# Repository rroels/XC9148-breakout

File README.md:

# Torex XC9148 Breakout Board

> [!WARNING]
> The information and material (code, designs, files, ...) are provided "AS IS". We make no representation or warranty of any kind, express or implied, regarding the accuracy, adequacy, validity, reliability, availability, or completeness of any information or material. Use this at your own risk.

> [!WARNING]
> At the time of writing this PCB has not even been produced yet, and as such, it has not even been tested yet! Once it has been properly tested, I will confirm that everything works as expected.

> [!WARNING]
> This board was designed for the XC9148G50CER variant of the XC9148. This has some characteristics that are important for the design of this breakout board (e.g. its output voltage, oscillation frequency and lack of bypass mode). 

## Introduction

This is a breakout board for the Torex XC9148 voltage convertor.

[https://product.torexsemi.com/en/series/xc9148](https://product.torexsemi.com/en/series/xc9148)

## Change Log

* v1.1
  * Increased pad sizes of XC9148 for easier soldering by hand
* v1.0
  * Initial design 

## Design Considerations

* Designed specifically for the XC9148G50CER variant of the XC9148
  * 0.9 - 6V input  
  * fixed 5V output
  * 1.2MHz oscillation frequency
  * no bypass mode

> [!WARNING]
> The 3.0MHz variations of the XC9148 will not work on this board!  

## Schematics 

## How to Obtain the Physical PCB

The Gerber file is in this repository (`gerbers/XC9148-breakout.zip`). Simply upload this file a PCB manufacturer of your choice (JLPCB, PCBWay, ...), and you they will make it for you for as low as \$5 for 5 pieces (with the cheapest shipping option, which can take a few weeks).

For JLCPCB, select the order number option where they will replace "JLCJLCJLCJLC" on the board with the actual order number.

> [!WARNING]
> Note that will still have to solder the components onto the PCB yourself!

## How to Edit Design

Everything you need to edit this design in KiCad 8 is included in the repository.

However, this project uses symbols, footprints and 3D models from [Component Search Engine](https://componentsearchengine.com/). Their license allows us to do pretty much whatever we want with them, except redistributing them. For this reason I can't include them in this repository.

If you would like to edit the design yourself, you will need to download the following component libraries from [https://componentsearchengine.com/](https://componentsearchengine.com/) (it's free!):

* [https://componentsearchengine.com/part-view/XC9148G50CER-G/Torex](https://componentsearchengine.com/part-view/XC9148G50CER-G/Torex)

From the downloaded zip files, move the content of the `KiCad` and `3D` subfolders into the project structure, so that the end-result looks like this:

The KiCad project is configured to look for these files in these locations, using relative paths, so no changes to the project itself are required.	

## Sources

* [https://product.torexsemi.com/en/series/xc9148](https://product.torexsemi.com/en/series/xc9148)

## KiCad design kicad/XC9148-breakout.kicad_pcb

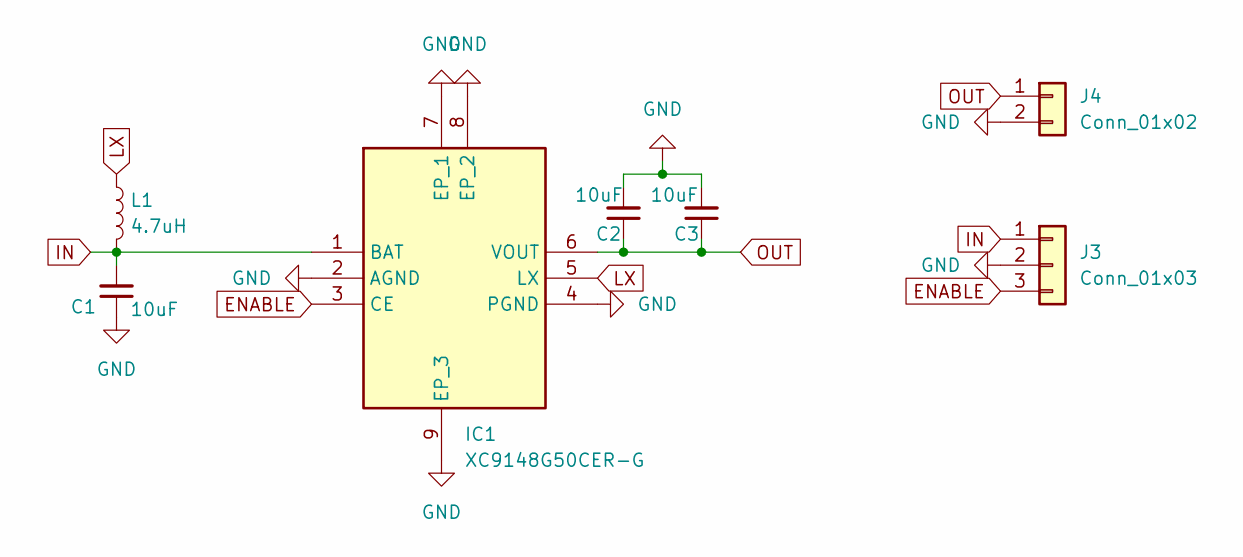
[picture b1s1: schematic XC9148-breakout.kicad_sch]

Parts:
C1, C2, C3: 10uF; C_0603_1608Metric_Pad1.08x0.95mm_HandSolder
IC1: XC9148G50CER-G; XC9147_8_USP-6C; Manufacturer_Part_Number XC9148G50CER-G; Mouser Part Number 865-XC9148G50CER-G
J3: Conn_01x03; PinHeader_1x03_P2.54mm_Vertical
J4: Conn_01x02; PinHeader_1x02_P2.54mm_Vertical
L1: 4.7uH; L_1008_2520Metric_Pad1.43x2.20mm_HandSolder

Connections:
ENABLE: IC1.3 (CE), J3.3
GND: C1.1, C2.2, C3.2, IC1.2 (AGND), IC1.4 (PGND), IC1.7 (EP_1), IC1.8 (EP_2), IC1.9 (EP_3), J3.2, J4.2
IN: C1.2, IC1.1 (BAT), J3.1, L1.2
LX: IC1.5 (LX), L1.1
OUT: C2.1, C3.1, IC1.6 (VOUT), J4.1

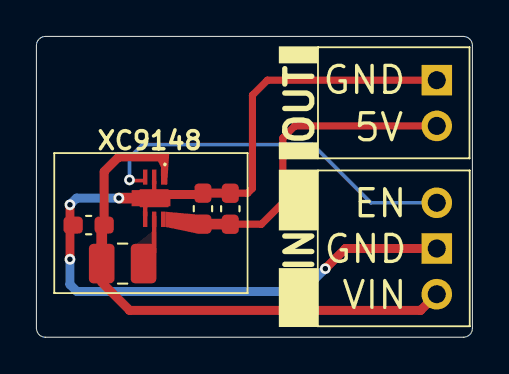
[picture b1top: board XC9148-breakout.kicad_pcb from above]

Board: 2 copper layers, 24.2 x 16.7 mm, 7 parts (0 on the bottom side), 5 nets.

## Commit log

2024-10-05 update XC9148 footprint for easier soldering by hand
